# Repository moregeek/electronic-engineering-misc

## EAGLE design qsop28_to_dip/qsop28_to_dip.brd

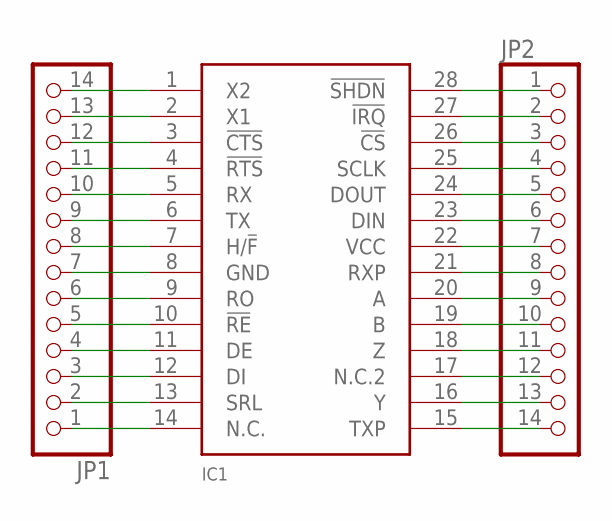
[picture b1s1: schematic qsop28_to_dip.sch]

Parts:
IC1: MAX314028SQSOP; 28QSOP
JP1, JP2: PINHD-1X14; 1X14

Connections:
unnamed: IC1.1 (X2), JP1.14
unnamed: IC1.2 (X1), JP1.13
unnamed: IC1.3 (!CTS), JP1.12
unnamed: IC1.4 (!RTS), JP1.11
unnamed: IC1.5 (RX), JP1.10
unnamed: IC1.6 (TX), JP1.9
unnamed: IC1.7 (H/!F), JP1.8
unnamed: IC1.8 (GND), JP1.7
unnamed: IC1.9 (RO), JP1.6
unnamed: IC1.10 (!RE), JP1.5
unnamed: IC1.11 (DE), JP1.4
unnamed: IC1.12 (DI), JP1.3
unnamed: IC1.13 (SRL), JP1.2
unnamed: IC1.14 (N.C.), JP1.1
unnamed: IC1.28 (!SHDN), JP2.1
unnamed: IC1.27 (!IRQ), JP2.2
unnamed: IC1.26 (!CS), JP2.3
unnamed: IC1.25 (SCLK), JP2.4
unnamed: IC1.24 (DOUT), JP2.5
unnamed: IC1.23 (DIN), JP2.6
unnamed: IC1.22 (VCC), JP2.7
unnamed: IC1.21 (RXP), JP2.8
unnamed: IC1.20 (A), JP2.9
unnamed: IC1.19 (B), JP2.10
unnamed: IC1.18 (Z), JP2.11
unnamed: IC1.17 (N.C.2), JP2.12
unnamed: IC1.16 (Y), JP2.13
unnamed: IC1.15 (TXP), JP2.14

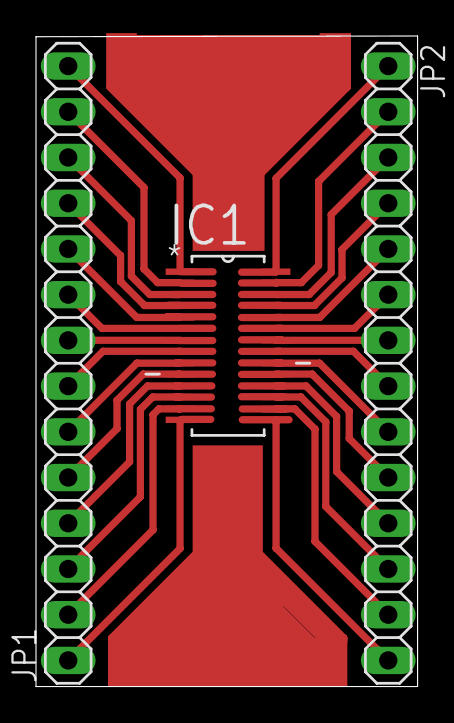
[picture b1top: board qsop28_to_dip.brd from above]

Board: 2 copper layers, 21.2 x 36.1 mm, 3 parts (0 on the bottom side), 28 nets.

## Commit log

2014-03-01 initial commit; qsop28 to dip adapter
